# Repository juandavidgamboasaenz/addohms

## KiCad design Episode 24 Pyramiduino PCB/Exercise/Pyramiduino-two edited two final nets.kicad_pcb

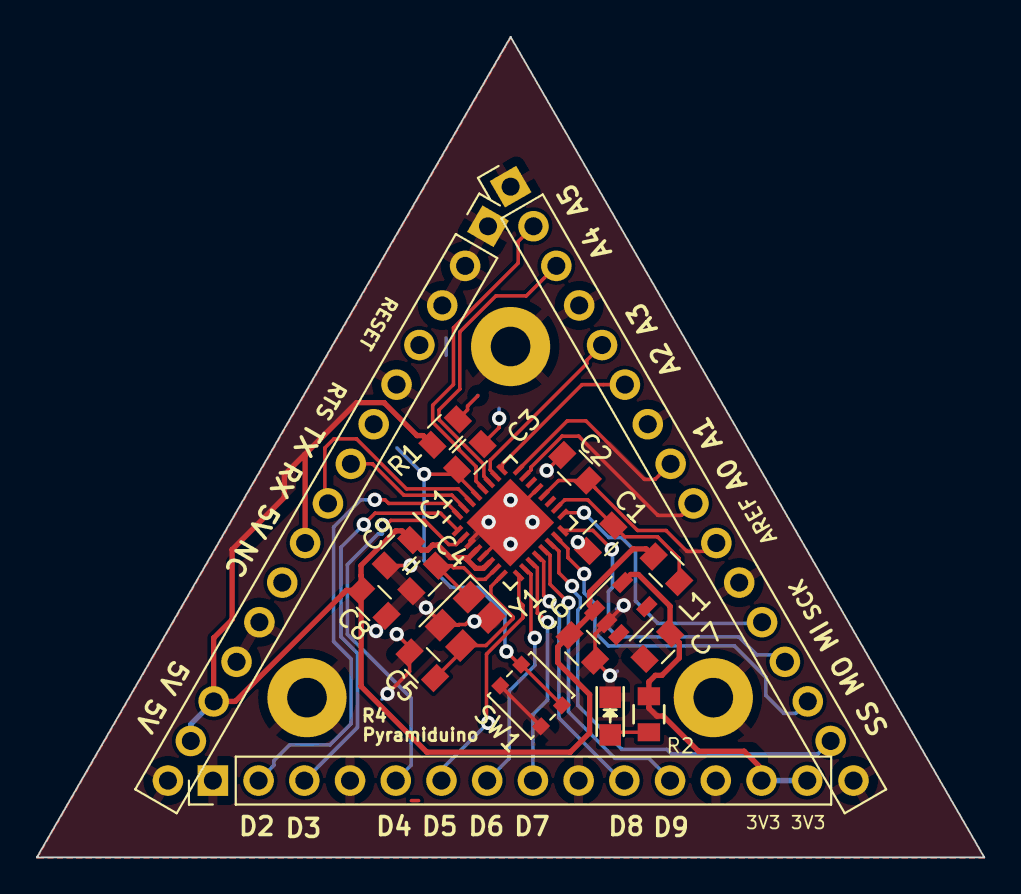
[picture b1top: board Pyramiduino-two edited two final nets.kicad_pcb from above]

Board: 2 copper layers, 52.6 x 45.6 mm, 23 parts (0 on the bottom side), 30 nets.

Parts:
C1, C3, C9: 100nF; C_0805
C2: 10nF; C_0805
C4, C5: 22pF; C_0805
C6, C7, C8: 1uF; C_0805
D1: LED; LED_0805
IC1: ATMEGA328-A; QFN-32-1EP_5x5mm_Pitch0.5mm-GND
L1: 10uH; C_0805
P1: CONN_01X16; Pin_Header_Straight_1x16_Pitch2.54mm
P2: CONN_01X14; Pin_Header_Straight_1x15_Pitch2.54mm
P3: CONN_01X14; Pin_Header_Straight_1x14_Pitch2.54mm
P4, P5, P6: CONN_01X01; MountingHole_2.2mm_M2_Pad
R1: 100K; C_0805
R2: 1k; C_0805
SW1: SW_PUSH; SW_SPST_PTS830
U1: MIC5504-3.3YM5; SOT-23-5
Y1: 16M; FA238-4pin_3.2x2.5mm_Offset

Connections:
+3V3: C7.2, P3.13, P3.14, R2.1, U1.5
/328-RX: IC1.30, P2.8
/328-TX: IC1.31, P2.7
/A0: IC1.23, P1.9
/A1: IC1.24, P1.8
/A2: IC1.25, P1.6
/A3: IC1.26, P1.5
/A4: IC1.27, P1.3
/A5: IC1.28, P1.2
/AREF: C2.1, IC1.20, P1.10
/D2: IC1.32, P3.2
/D3: IC1.1, P3.3
/D4: IC1.2, P3.5
/D5: IC1.9, P3.6
/D6: IC1.10, P3.7
/D7: IC1.11, P3.8
/D8: IC1.12, P3.10
/D9: IC1.13, P3.11
/MISO: IC1.16, P1.13
/MOSI: IC1.15, P1.14
/RESET: C3.1, IC1.29, P2.4, R1.2, SW1.2
/RTS: C3.2, P2.6
/SCK: IC1.17, P1.12
/SS: IC1.14, P1.15
/X_N: C5.2, IC1.8, Y1.3
/X_P: C4.2, IC1.7, Y1.1
GND: C1.2, C2.2, C4.1, C5.1, C6.1, C7.1, C8.2, C9.2, D1.1, IC1.3, IC1.5, IC1.21, P1.1, P1.4, P1.7, P1.11, P1.16, P2.1, P2.2, P2.3, P2.5, P2.11, P2.12, P2.15, P3.1, P3.4, P3.9, P3.12, P4.1, P5.1, P6.1, SW1.1, U1.2, Y1.2, Y1.4
unnamed: C1.1, IC1.18, L1.1
unnamed: D1.2, R2.2
VCC: C6.2, C8.1, C9.1, IC1.4, IC1.6, L1.2, P2.9, P2.13, P2.14, R1.1, U1.1

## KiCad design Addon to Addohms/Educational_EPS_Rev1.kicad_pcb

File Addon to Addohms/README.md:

Just to share some knowledge and say thanks, this a thesis project I created some years ago. Inspired too much in your content and was almost a success, (Pandemic here) the good think is that it was a good prototipe, some fixes were needed also related with the reset and some other pins. The project was made in Altium but I'll share with you the link if you have want to check it out. Also an import made to KiCad with no schematics. Will improve the design and also export it to a "cheaper" software. Altium is expensive.

Wish you success! 

Here is the link to it. 

https://drive.google.com/drive/folders/10YTGg6eOegAFkpwsx3XXrDEhwtR_7O-0?usp=sharing

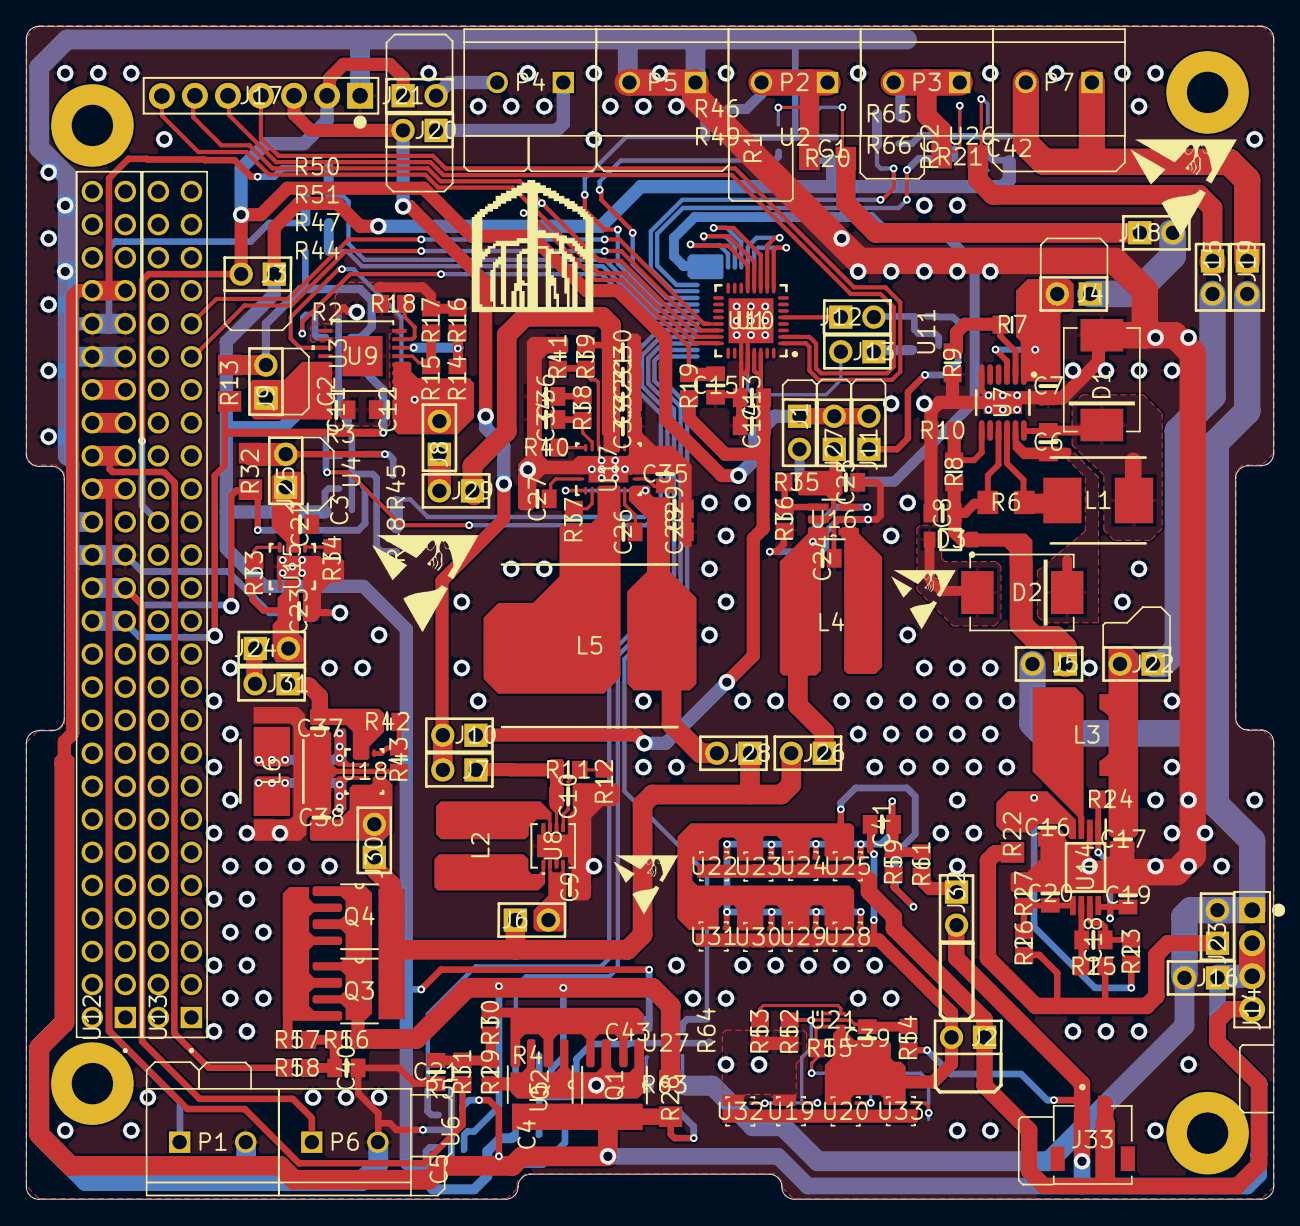
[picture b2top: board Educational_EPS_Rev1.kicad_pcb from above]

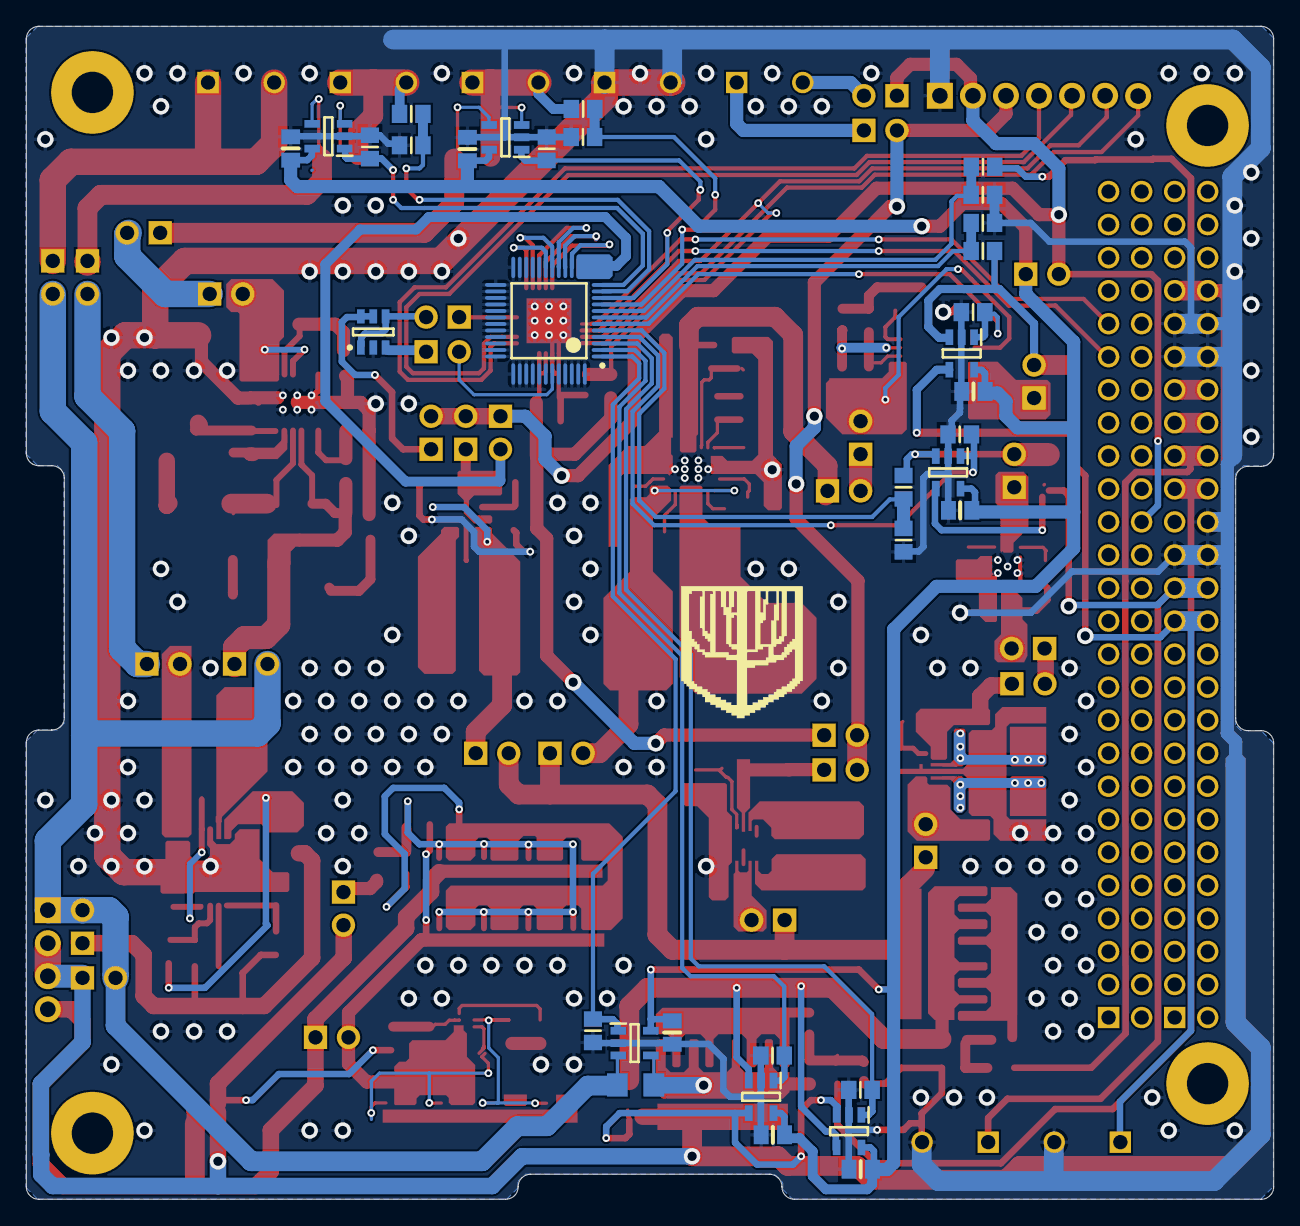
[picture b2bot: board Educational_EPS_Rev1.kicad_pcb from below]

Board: 2 copper layers, 95.9 x 90.2 mm, 198 parts (34 on the bottom side), 122 nets.

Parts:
C1, C2, C3, C4, C5, C6, C7, C8, C9, C10, C11, C12, C13, C14, C15, C16, C17, C18, C19, C20, C21, C22, C23, C24, C25, C26, C27, C28, C29, C30, C31, C32, C33, C34, C35, C36, C37, C38, C39, C40, C41, C42, C43: SMD-0805C
D1, D2: DO-214AB
D3: ONSC-SOD-123-2-425-04_V
DH1, DH2, DH3, DH4: Drill Hole PCI-104 Flat
J1, J2, J3, J4, J5, J6, J7, J8, J9, J10, J11, J12, J13, J15, J16, J18, J19, J20, J21, J22, J23, J24, J25, J26, J27, J28, J29, J30, J31, J32: MHDR1X2
J14: 732-5317
J17: 732-5320
J33: *JST_S2B-ZR-SM4A-TF(LF)(SN)_S2B-ZR-SM4A-TF(LF)(SN)(Primary)
L1: SRP7028A
L2, L3: SRR5028
L4: SRR6038
L5: SRP1265A
L6: IHLP-2020BZ
P1, P2, P3, P4, P5, P6, P7: A113320
Q1, Q2, Q3, Q4: SOIC127P600X175-8N
R1, R2, R3, R4, R5, R7, R8, R9, R10, R11, R12, R14, R15, R16, R17, R18, R19, R23, R24, R25, R26, R27, R29, R30, R31, R33, R34, R35, R36, R37, R38, R39, R40, R41, R42, R43, R44, R45, R46, R47, R48, R49, R50, R51, R52, R53, R54, R55, R56, R57, R58, R59, R61, R62, R64, R65, R66: RESC2012N
R6, R13, R20, R21, R22, R28, R32, R63: RESC3216X90
U1: ADI-SU-48_N
U2, U3, U4, U5, U6, U26, U27: SOT95P280X145-5N
U7: LT-MSE-12-EDP_N
U8: DFN-8_DD-L
U9: 21-0108G_U14E-00
U10: TI-RHB32-3450X3450TP_N
U11: TI-DBV6_N
U12, U13: HDRV52W64P254_26X2_6654X495H1359
U14: SOP65P640X120-8N
U15: DRB8-2400X1650TP
U16: DDC0006A_N
U17: RHL0020A
U18: RNC0014A
U19, U20, U22, U23, U24, U25, U28, U29, U30, U31, U32, U33: DQK6
U21: DSE6

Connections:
3V3SUPP: J7.2, J10.2, J17.A3, J20.2
5VOV: R14.1, R16.2, U9.5
5VSUPP: J1.1, J3.2, J11.2, J17.A2, J21.1, J27.2, U13.32
5VSUPPINA: C1.2, C2.2, C3.2, C4.2, C5.2, C42.2, C43.2, J3.1, U2.5, U3.5, U4.5, U5.5, U6.5, U26.5, U27.5
-VBATT: J2.1, J14.A3, J33.2, U22.1, U22.2, U22.5, U22.6, U22.7, U23.1, U23.2, U23.5, U23.6, U23.7, U24.1, U24.2, U24.5, U24.6, U24.7, U25.1, U25.2, U25.5, U25.6, U25.7
BOOSTX: C6.2, D2.1, U7.11
CMA0: U1.15, U10.13
CMA1: U1.16, U10.12
CMA2: U1.17, U10.11
CMA3: U1.18, U10.10
CMA4: U1.19, U10.9
COUT: R52.2, U19.3, U21.2, U32.3
DATA: J13.2, U1.43
DATADC: J12.1, U10.5
DOUT: R55.2, U20.3, U21.3, U33.3
GND: C1.1, C2.1, C3.1, C4.1, C5.1, C7.1, C8.1, C9.1, C10.1, C11.1, C12.1, C13.2, C14.2, C15.1, C16.1, C17.1, C19.1, C20.1, C21.1, C22.1, C23.1, C24.1, C25.1, C27.1, C28.1, C29.1, C30.1, C31.1, C32.1, C33.1, C34.1, C35.1, C36.1, C37.1, C38.1, C40.1, C42.1, C43.1, D1.2, J17.A1, P1.2, P5.1, P5.2, P6.2, R1.2, R2.2, R3.2, R4.2, R5.2, R9.1, R10.1, R12.1, R16.1, R17.1, R18.1, R27.1, R34.1, R36.1, R40.1, R41.1, R43.1, R47.1, R48.1, R49.1, R51.1, R52.1, R53.2, R62.2, R64.2, R66.1, U1.20, U1.21, U1.22, U1.23, U1.24, U1.25, U1.26, U1.27, U1.28, U1.29, U1.30, U1.31, U1.32, U1.33, U1.34, U1.35, U1.36, U1.37, U1.38, U1.39, U1.40, U1.41, U1.42, U1.44, U1.45, U1.46, U1.47, U1.48, U2.2, U3.2, U4.2, U5.2, U6.2, U7.6, U7.13, U8.3, U8.8, U8.9, U9.7, U9.8, U9.9, U9.15, U10.27, U10.28, U10.33, U11.2, U12.29, U12.30, U12.32, U12.41, U12.42, U12.43, U12.44, U14.2, U15.1, U15.4, U15.9, U16.2, U17.11, U17.12, U17.20, U17.21, U18.2, U18.9, U18.10, U19.4, U19.8, U26.2, U27.2, U32.4, U32.8
GNDB: C39.1, C41.1, J2.2, R55.1, U20.4, U20.8, U21.4, U28.1, U28.2, U28.5, U28.6, U28.7, U29.1, U29.2, U29.5, U29.6, U29.7, U30.1, U30.2, U30.5, U30.6, U30.7, U31.1, U31.2, U31.5, U31.6, U31.7, U33.4, U33.8
GNDD: U19.1, U19.2, U19.5, U19.6, U19.7, U20.1, U20.2, U20.5, U20.6, U20.7, U32.1, U32.2, U32.5, U32.6, U32.7, U33.1, U33.2, U33.5, U33.6, U33.7
I2CCLK: U10.21, U13.43
I2CDATA: U10.22, U13.41
I-SPX+-: J4.1, J18.2
I-SPX+-_2: J15.2, J22.1
I-SPZ-: J5.2, J14.A0, J16.2, J19.2, J23.2, R63.1, U27.3
I-SPZ- RBF_Bridge: Q1.1, Q1.3, Q2.1, Q2.3, R29.2, R63.2, U27.4
ICHGX: L1.2, R6.2, U7.10
MIBATB: R64.1, U1.1, U27.1
MIBATC: R4.1, U1.2, U5.1
MIBATD: R5.1, U1.3, U6.1
MIPRO3V3: R3.1, U1.4, U4.1
MIPRO5V: R2.1, U1.6, U3.1
MISPX+: R1.1, U1.10, U2.1
MISPX+_2: R62.1, U1.12, U26.1
MVBAT: R50.1, R51.2, U1.8
MVPRO3V3: R45.1, R48.2, U1.5
MVPRO5V: R44.1, R47.2, U1.7
MVSPX+: R46.1, R49.2, U1.9
MVSPX+2: R65.1, R66.2, U1.11
NCDS: R58.1, U12.35, U12.36
NCRBF: R31.1, U12.33, U12.34
NODS: U12.39, U12.40
NORBF: U12.37, U12.38
NetC6_1: C6.1, D1.1, L1.1, U7.12
NetC7_2: C7.2, J4.2, R7.2, U7.1, U7.3
NetC8_2: C8.2, D3.1, J5.1, R6.1, R8.2, U7.9
NetC9_2: C9.2, J6.2, U8.2, U8.4
NetC10_2: C10.2, J7.1, R11.2, U8.6
NetC11_2: C11.2, J9.1, U9.12, U9.13, U9.14
NetC12_2: C12.2, J8.2, R14.2, R15.2, U9.1, U9.2, U9.3, U9.10
NetC13_1: C13.1, C14.1, J10.1, R19.2, U10.29, U10.30
NetC16_2: C16.2, R22.1, R23.2, U14.4
NetC17_2: C17.2, J22.2, L3.1, R24.1
NetC18_1: C18.1, R25.1, U14.6
NetC18_2: C18.2, R23.1, U14.7
NetC19_2: C19.2, R24.2, U14.1, U14.8
NetC20_2: C20.2, R26.1, R27.2, U14.5
NetC21_2: C21.2, R29.1, R30.1, R31.2
NetC22_2: C22.2, J25.1, U15.6, U15.7
NetC23_2: C23.2, J24.2, R33.2, U15.2, U15.3
NetC24_2: C24.2, J26.1, L4.2, U16.3, U16.6
NetC25_2: C25.2, J27.1, R35.2, U16.5
NetC26_1: C26.1, U17.8
NetC26_2: C26.2, L5.2, R37.2, U17.4, U17.5, U17.6, U17.7
NetC27_2: C27.2, U17.1
NetC28_2: C28.2, C29.2, J28.2, L5.1, U17.2, U17.9
NetC30_2: C30.2, C31.2, C32.2, C33.2, J29.1, R39.2, U17.14, U17.15, U17.16
NetC34_2: C34.2, R38.2, U17.18
NetC35_2: C35.2, U17.10
NetC36_2: C36.2, R38.1
NetC37_2: C37.2, J31.1, R42.2, U18.12, U18.13, U18.14
NetC38_2: C38.2, J30.2, U18.4, U18.5, U18.6, U18.7, U18.8
NetC39_2: C39.2, R54.1, U21.5
NetC40_2: C40.2, R56.1, R57.1, R58.2
NetC41_2: C41.2, R59.2, R61.2, U22.3, U23.3, U24.3, U25.3, U28.3, U29.3, U30.3, U31.3
NetD2_2: D2.2, D3.2
NetJ1_2: J1.2, U1.13, U1.14
NetJ11_1: J11.1, U11.5, U11.6
NetJ12_2: J12.2, U11.1, U11.4
NetJ13_1: J13.1, U11.3
NetJ19_1: J19.1, P7.1, P7.2
NetJ20_1: J20.1, P4.1
NetJ21_2: J21.2, P4.2
NetJ23_1: J23.1, R22.2, R25.2, R26.2
NetJ32_1: J32.1, R61.1
NetL2_1: L2.1, U8.1
NetL2_2: L2.2, U8.7
NetL3_2: L3.2, U14.3
NetL4_1: L4.1, U16.1
NetL6_1: L6.1, U18.3
NetL6_2: L6.2, U18.1
NetQ1_2: Q1.2, Q1.4, Q2.2, Q2.4, R30.2
NetQ3_2: Q3.2, Q3.4, Q4.2, Q4.4, R57.2
NetR7_1: R7.1, R9.2, U7.2
NetR11_1: R11.1, R12.2, U8.5
NetR15_1: R15.1, R17.2, U9.4
NetR18_2: R18.2, U9.6
NetR33_1: R33.1, U15.8
NetR34_2: R34.2, U15.5
NetR35_1: R35.1, R36.2, U16.4
NetR37_1: R37.1, U17.3
NetR39_1: R39.1, R41.2, U17.17
NetR40_2: R40.2, U17.19
NetR42_1: R42.1, R43.2, U18.11
NetR53_1: R53.1, U21.6
NetR59_1: R59.1, U22.4, U22.8, U23.4, U23.8, U24.4, U24.8, U25.4, U25.8, U28.4, U28.8, U29.4, U29.8, U30.4, U30.8, U31.4, U31.8
RBF_CD_Bridge: Q3.1, Q3.3, Q4.1, Q4.3, R28.2, R56.2, U5.3, U6.4
SBWTCK: J17.A7, U10.24
SBWTDIO: C15.2, J17.A6, R19.1, U10.23
UARTRX: J17.A4, U10.1
UARTTX: J17.A5, U10.2
VBAT: R8.1, R10.2, U7.7
VBATT: J14.A1, J14.A2, J16.1, J32.2, J33.1, Q1.5, Q1.6, Q1.7, Q1.8, Q2.5, Q2.6, Q2.7, Q2.8, R28.1, R50.2, R54.2, U5.4, U6.3, U12.45, U12.46
VBUSES: J6.1, J26.2, J28.1, J30.1, Q3.5, Q3.6, Q3.7, Q3.8, Q4.5, Q4.6, Q4.7, Q4.8
VPCM3V3: J24.1, J31.2
VPCM5V: J8.1, J29.2
VPRO3V3: J25.2, R32.1, R45.2, U4.3
VPRO3V3B: P6.1, R32.2, U4.4, U12.27, U12.28
VPRO5V: J9.2, R13.1, R44.2, U3.3
VPRO5VB: P1.1, R13.2, U3.4, U12.25, U12.26
VSPX+: P2.1, P2.2, R20.1, R46.2, U2.3
VSPX+2: P3.1, P3.2, R21.1, R65.2, U26.3
VSPX+-: J18.1, R20.2, U2.4
VSPX+-2: J15.1, R21.2, U26.4

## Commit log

2024-09-13 Correction of reset, MOSI and MISO nets.
    Given the Piramiduino-two schematics some changes were made in order order to correct and improve the PCB project. Also some Vias were deleted and other connections made.
2024-09-13 Update content and add some good files for you to check it out. Google Drive relate content in Addon to Addohms folder.
    Thanks for the ideas and inspiration. Remember to make it good and always with a grat smile and purpouse.
2024-09-13 update zip files
2024-09-24 Added back ups generated from KiCad app file.
